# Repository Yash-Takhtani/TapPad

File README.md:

# TapPad
TapPad speeds up annoying tasks. You can use the keys to assign custom macros on your device or use the rotary switch to control media. It has a customizable 0.91 inch OLED status display and a LED indicator.

# PCB Design 
The PCB was made on Kicad. It connects all 5 switches, rotory encoder switch, LED and the OLED display, to the Seeduino board. 
Schematic and PCB layout is as follows - 

# Case design 
Case designed on fusion for the pcb having 5 switches, one rotary encoder, an OLED display and the LED indicator with a USB-C port on the right side. It assembles via 4 magnets flushed inside the corners of the base and lid. 
It has grooves and extruded covers to fit the OLED display, rotary encoder and seeeduino USB-C. 
Triangular designs have been engraved along with a extruding "Tap Pad!" text to give it a unique design.  

# Firmware
 - The firmware is made via QMK. It assigns the function keys from F13 to F20 to the 5 switches and rotary. 
 - [OLED Display Control](https://github.com/Yash-Takhtani/TapPad/blob/main/tappad.py) can be used to control the rgb led.
 - The actions on button presses can be configured through [TapPad keymap](https://github.com/Yash-Takhtani/TapPad/blob/main/TapPad keymap.py). In this example I control my Smart LED bulb, the rgb led on the board, my pc wallpaper and open some apps/websites with the keypresses.
 - The buttons have been mapped to function keys as follows - 
   - Key1 - F13
   - Key2 - F14
   - Key3 - F15
   - Key4 - F16
   - Key5 - F17
   - Roatary- - F18
   - Roatary+ - F19
   - Roatary Button - F20
**NOTE -** The python files require variable dependencies like the bulb api might bight be different for your bulb and the actions you want the buttons to make might be of your choice. In that case its recomended you edit 'TapPad keymap.py' file according to your needs and run it with python. Also the 'led.py' only allows you to control the RGB LED on the board with python.  

# Bill of Materials
Hackpad kit -
- 1x unsoldered Seeed XIAO RP2040
- 5x MX style switches
- 1x EC11 Rotary encoder
- 1x 0.91 inch OLED display
- 5x white blank DSA keycaps
- 1x SK6812 MINI-E LEDs

To be purchased with the grant - 
- PCB (from external PCB manufacturer like JLCPCB)
- 3D printed case and rotary cap from Printing Legion

# Build
**I completed the build!**

During the build I slightly misplaced the oled display due to which i had to modify the display cutout with my coldering iron. It kinda left burnt marks. I have added extra clearances to the CAD.

# Next Steps
Configurable OLED python script

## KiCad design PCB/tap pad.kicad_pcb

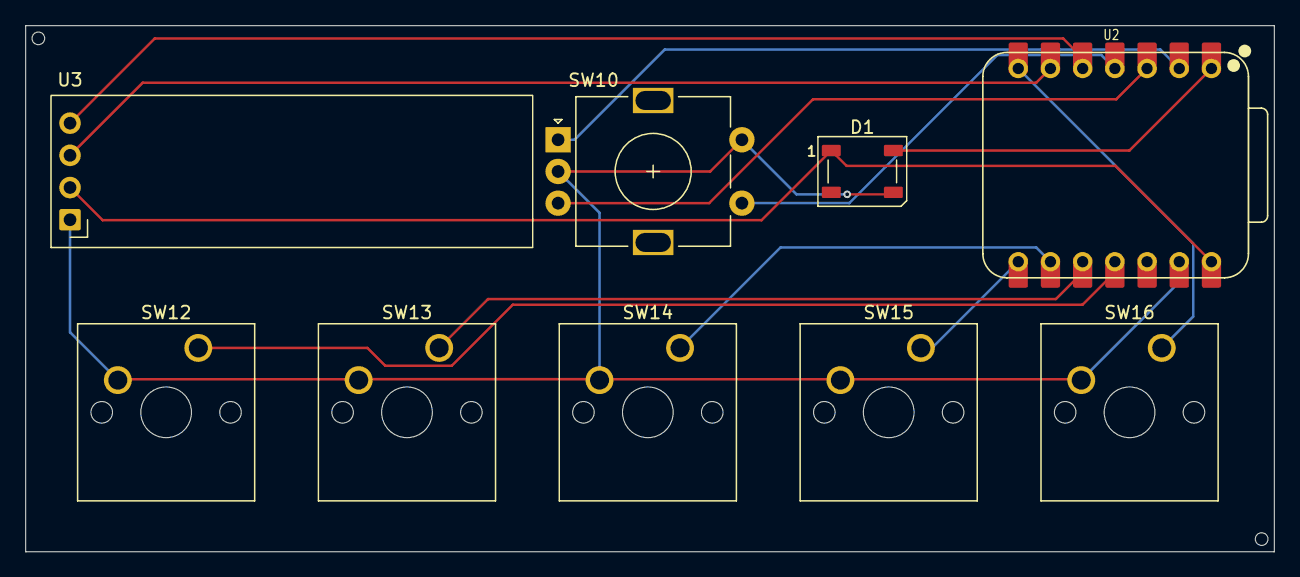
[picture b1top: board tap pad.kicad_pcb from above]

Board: 2 copper layers, 98.5 x 41.5 mm, 9 parts (0 on the bottom side), 13 nets.

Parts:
D1: WS2812B; LED_WS2812B_PLCC4_5.0x5.0mm_P3.2mm
SW10: RotaryEncoder_Switch; RotaryEncoder_Alps_EC11E-Switch_Vertical_H20mm
SW12, SW13, SW14, SW15, SW16: SW_Push; SW_Cherry_MX_1.00u_PCB
U2: XIAO-ESP32-C3-DIP
U3: ER_OLEDM0.91_1x-I2C

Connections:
unnamed: D1.4 (DIN), U2.1 (PA02_A0_D0)
unnamed: D1.1 (VDD), U2.14 (5V), U3.2 (VCC)
unnamed: D1.3 (VSS), SW10.C, SW10.S2, SW12.2, SW13.2, SW14.2, SW15.2, SW16.2, U2.13 (GND), U3.1 (GND)
unnamed: SW10.A, U2.2 (PA4_A1_D1)
unnamed: SW13.1, U2.10 (PA5_A9_D9_MISO)
unnamed: SW12.1, U2.11 (PA6_A10_D10_MOSI)
unnamed: SW14.1, U2.9 (PA7_A8_D8_SCK)
unnamed: U2.5 (PA8_A4_D4_SDA), U3.4 (SDA)
unnamed: U2.6 (PA9_A5_D5_SCL), U3.3 (SCL)
unnamed: SW10.B, U2.3 (PA10_A2_D2)
unnamed: SW10.S1, U2.4 (PA11_A3_D3)
unnamed: SW16.1, U2.7 (PB08_A6_D6_TX)
unnamed: SW15.1, U2.8 (PB09_A7_D7_RX)
